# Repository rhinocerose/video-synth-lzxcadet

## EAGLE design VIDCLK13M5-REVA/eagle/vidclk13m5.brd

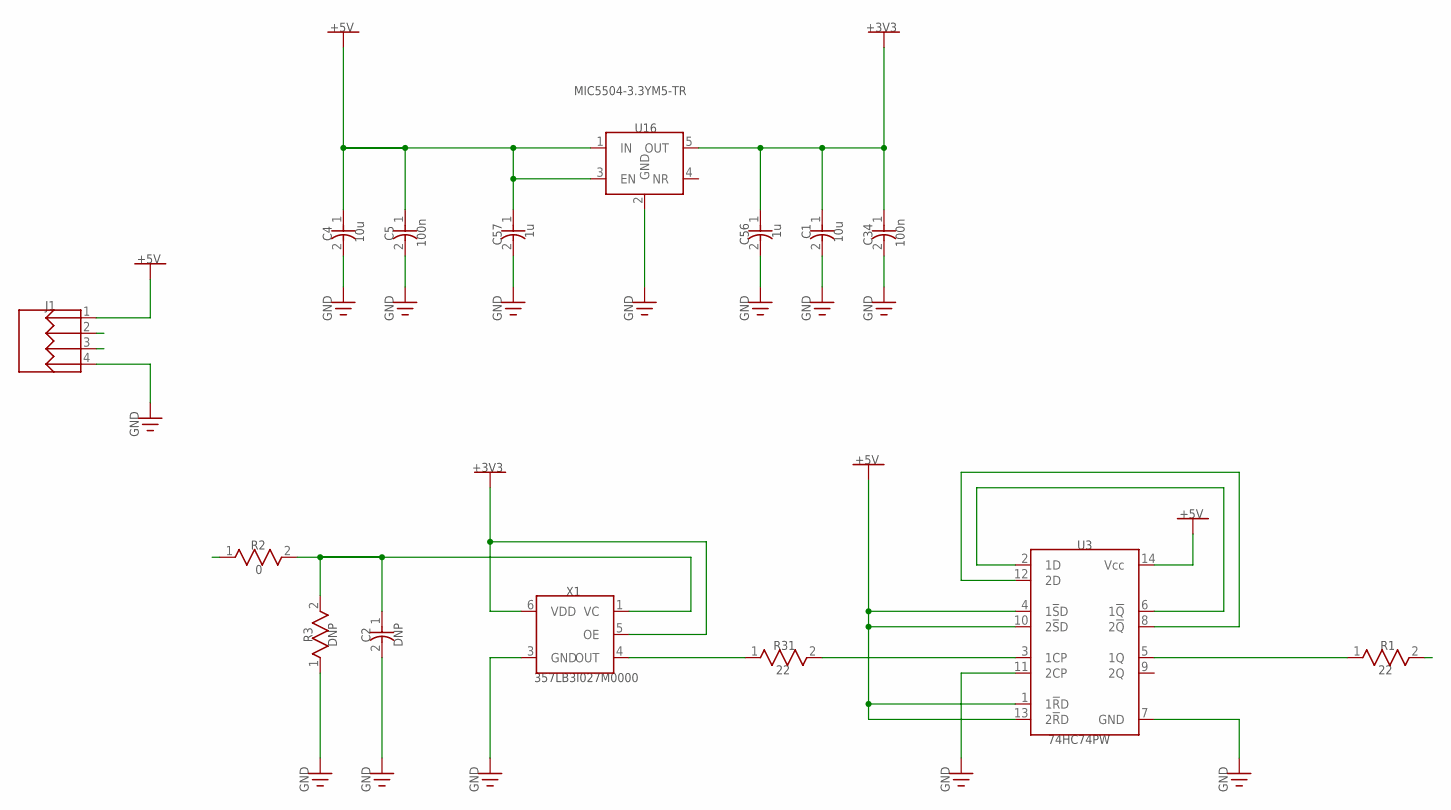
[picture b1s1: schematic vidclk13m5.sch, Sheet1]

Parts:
C1, C4: 10u; CAP_0805
C2: DNP; CAP_0603
C5, C34: 100n; CAP_0603
C56, C57: 1u; CAP_0603
J1: 644456-4; HDR-1X4T/2.54/10X2
R1, R31: 22; RES_0603_M
R2: 0; RES_0603_M
R3: DNP; RES_0603_M
U3: 74HC74PW; TSSOP-14
U16: MIC5504-3.3YM5-TR; SOT23-5
X1: 357LB3I027M0000; CSX-750V

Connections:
CLK: J1.3, R1.2
GND: C1.2, C2.2, C4.2, C5.2, C34.2, C56.2, C57.2, J1.4, R3.1, U3.7 (GND), U3.11 (2CP), U16.2 (GND), X1.3 (GND)
Net_1: U3.8 (2!Q!), U3.12 (2D)
Net_2: U3.2 (1D), U3.6 (1!Q!)
Net_3: C1.1, C34.1, C56.1, U16.5 (OUT), X1.5 (OE), X1.6 (VDD)
Net_4: R1.1, U3.5 (1Q)
Net_5: R31.1, X1.4 (OUT)
Net_6: R31.2, U3.3 (1CP)
Net_7: C2.1, R2.2, R3.2, X1.1 (VC)
Net_8: C4.1, C5.1, C57.1, J1.1, U3.1 (1!R!D), U3.4 (1!S!D), U3.10 (2!S!D), U3.13 (2!R!D), U3.14 (Vcc), U16.1 (IN), U16.3 (EN)
VC: J1.2, R2.1

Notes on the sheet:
R31
+5V
357LB3I027M0000
GND
74HC74PW
+3V3
10u
DNP
C56
C57
U16
MIC5504-3.3YM5-TR
100n
C34

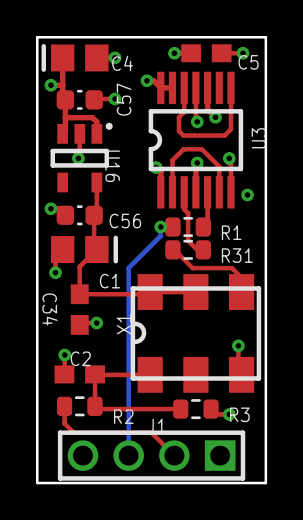
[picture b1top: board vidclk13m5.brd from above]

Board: 4 copper layers, 12.7 x 24.8 mm, 15 parts (0 on the bottom side), 11 nets.

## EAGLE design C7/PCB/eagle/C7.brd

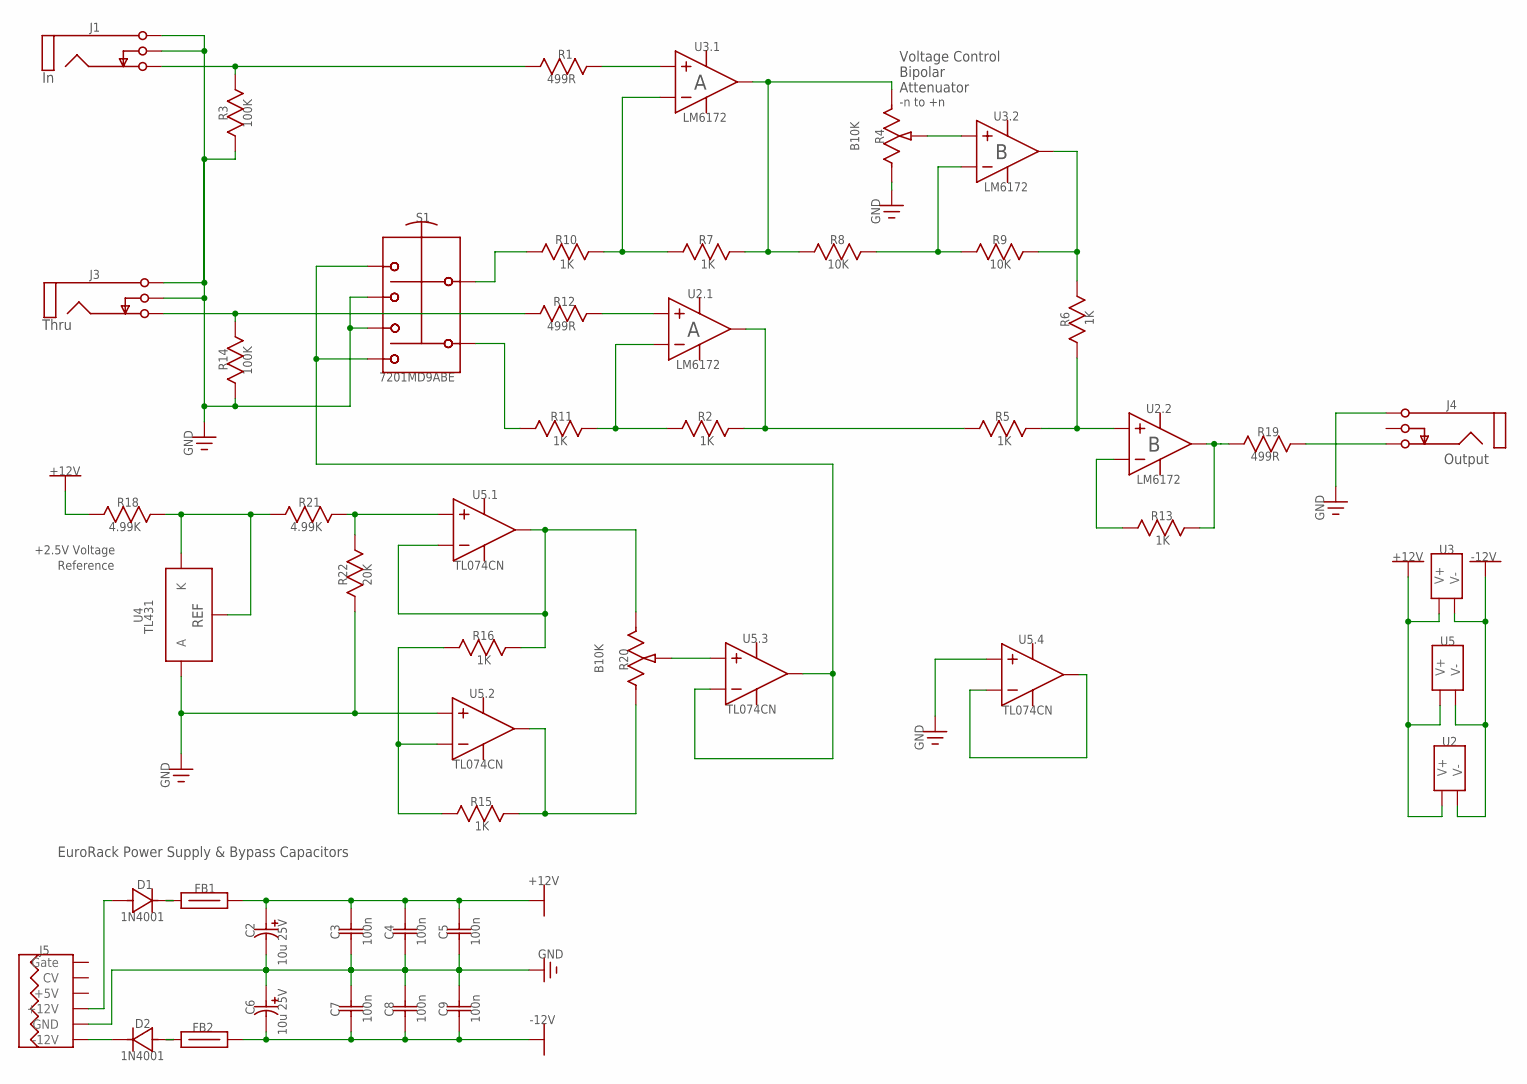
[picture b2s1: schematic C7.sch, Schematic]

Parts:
C2, C6: 10u 25V; CAPPR-2/5.08
C3, C4, C5, C7, C8, C9: 100n; CAP-2.54/6.6X3
D1, D2: 1N4001; DO-41
FB1, FB2: 68R; FB-10.16/4.45X3.5
J1, J3: PJ302M
J4: PJ302M_2; PJ302M
J5: EUROPWR16; IDC16M
R1, R12, R19: 499R; RES-7.62/5.1X2.5
R2, R5, R6, R7, R10, R11, R13, R15, R16: 1K; RES-7.62/5.1X2.5
R3, R14: 100K; RES-7.62/5.1X2.5
R4, R20: B10K; ALPHA9H
R8, R9: 10K; RES-7.62/5.1X2.5
R18, R21: 4.99K; RES-7.62/5.1X2.5
R22: 20K; RES-7.62/5.1X2.5
S1: 7201MD9ABE; 7201-A
U2, U3: LM6172; DIP-8
U4: TL431; TO-92-100R
U5: TL074CN; DIP-14

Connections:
0V: C2.2 (MINUS), C3.2, C4.2, C5.2, C6.1 (PLUS), C7.1, C8.1, C9.1, J1.1A (Sleeve), J1.1B (Sleeve), J1.2A (Switch), J1.2B (Switch), J3.1A (Sleeve), J3.1B (Sleeve), J3.2A (Switch), J3.2B (Switch), J4.1A (Sleeve), J4.1B (Sleeve), J5.3 (GND), J5.4 (GND), J5.5 (GND), J5.6, J5.7, J5.8, R3.1 (A), R4.1 (CCW), R14.1 (A), R22.2 (B), S1.3, S1.3B (3), S1.4, S1.4B (4), U4.2 (A), U5.5 (IN+), U5.12 (IN+)
+12V: C2.1 (PLUS), C3.1, C4.1, C5.1, FB1.2, R18.2 (B), U2.8 (V+), U3.8 (V+), U5.4 (V+)
-12V: C6.2 (MINUS), C7.2, C8.2, C9.2, FB2.2, U2.4 (V-), U3.4 (V-), U5.11 (V-)
BUFFERED_VC_TO_FADER: R6.2 (B), R9.2 (B), U3.7 (OUT)
Net_0: R12.2 (B), U2.3 (IN+)
Net_1: D2.2 (A), FB2.1
Net_2: D1.1 (K), FB1.1
Net_3: R2.1 (A), R11.2 (B), U2.2 (IN-)
Net_4: R16.2 (B), R20.1 (CCW), U5.1 (OUT), U5.2 (IN-)
Net_5: D2.1 (K), J5.1 (-12V), J5.2 (-12V)
Net_6: R15.2 (B), R20.3 (CW), U5.7 (OUT)
Net_7: R20.2 (W), U5.10 (IN+)
Net_8: S1.1, S1.1B (1), S1.6, S1.6B (6), U5.8 (OUT), U5.9 (IN-)
Net_9: J5.11 (+5V), J5.12 (+5V)
Net_10: R1.2 (B), U3.3 (IN+)
Net_11: J5.13 (CV), J5.14 (CV)
Net_21: R13.2 (B), R19.1 (A), U2.7 (OUT)
Net_23: R4.2 (W), U3.5 (IN+)
Net_24: R2.2 (B), R5.1 (A), U2.1 (OUT)
Net_25: R13.1 (A), U2.6 (IN-)
Net_26: R5.2 (B), R6.1 (A), U2.5 (IN+)
Net_27: R15.1 (A), R16.1 (A), U5.6 (IN-)
Net_28: R10.1 (A), S1.2 (COMM), S1.2B (COMM)
Net_29: U5.13 (IN-), U5.14 (OUT)
Net_30: R21.1 (A), R22.1 (A), U5.3 (IN+)
Net_31: R11.1 (A), S1.5 (COMM), S1.5B (COMM)
Net_32: J4.2A (Switch), J4.2B (Switch)
Net_33: D1.2 (A), J5.9 (+12V), J5.10 (+12V)
Net_34: J4.3A (Tip), J4.3B (Tip), R19.2 (B)
Net_35: J5.15 (Gate), J5.16 (Gate)
Net_50: R18.1 (A), R21.2 (B), U4.1 (K), U4.3 (REF)
Net_52: R7.1 (A), R10.2 (B), U3.2 (IN-)
Net_53: R4.3 (CW), R7.2 (B), R8.1 (A), U3.1 (OUT)
Net_54: R8.2 (B), R9.1 (A), U3.6 (IN-)
Net_58: J1.3A (Tip), J1.3B (Tip), R1.1 (A), R3.2 (B)
Net_64: J3.3A (Tip), J3.3B (Tip), R12.1 (A), R14.2 (B)

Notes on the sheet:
EuroRack Power Supply & Bypass Capacitors
Output
+2.5V Voltage
Attenuator
Bipolar
-n to +n
Reference
Thru
Voltage Control
10u 25V
100n
1N4001
FB1
FB2
GND
+12V
-12V
499R
100K
B10K
10K
R10
R11
R12
R13
R14
R15
R16
7201MD9ABE
R18
4.99K
R19
R20
R21
R22
20K
U2.1
LM6172
U2.2
U3.1

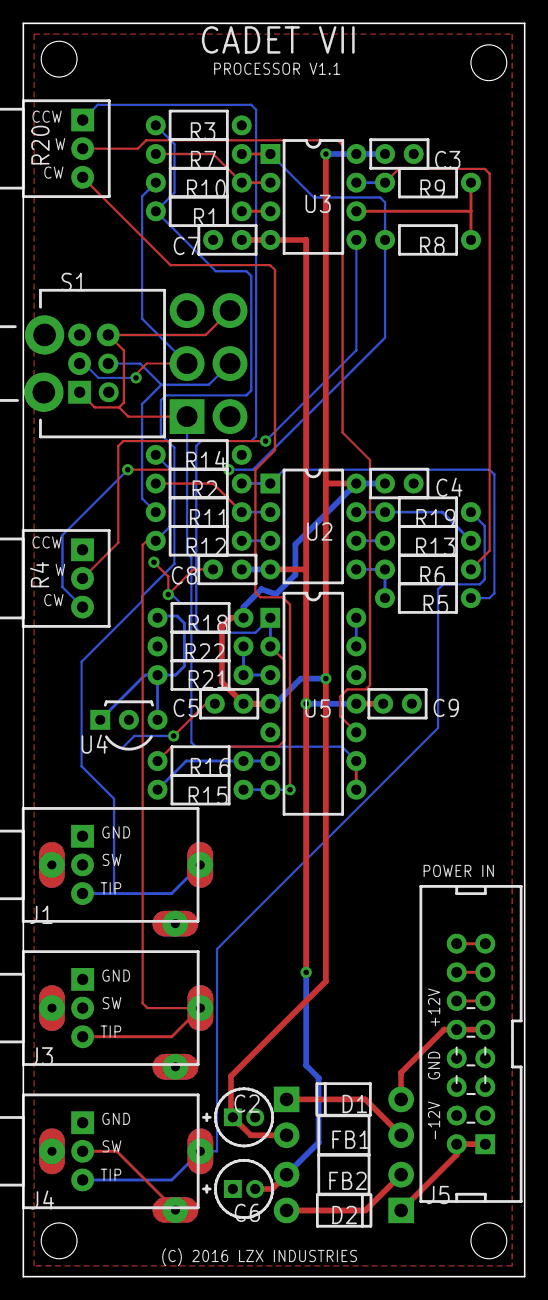
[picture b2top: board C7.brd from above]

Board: 2 copper layers, 44.5 x 111.1 mm, 42 parts (0 on the bottom side), 36 nets.

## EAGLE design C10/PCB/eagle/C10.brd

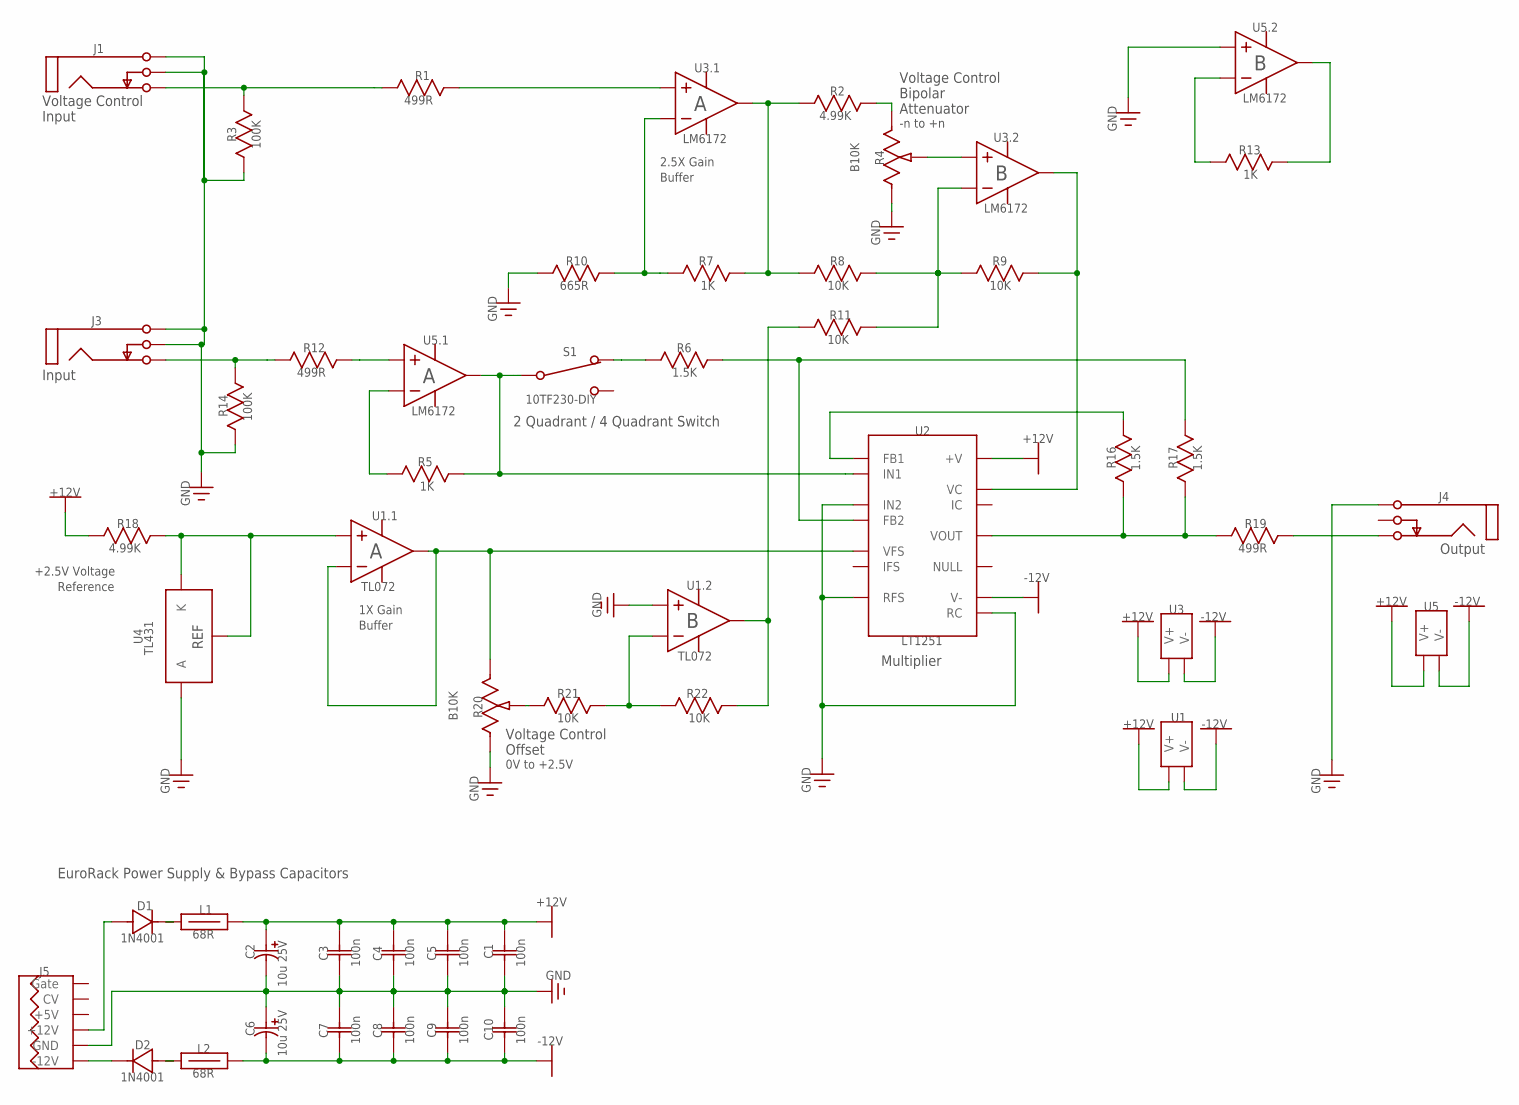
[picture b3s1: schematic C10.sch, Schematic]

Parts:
C1, C3, C4, C5, C7, C8, C9, C10: 100n; CAP-2.54/6.6X3
C2, C6: 10u 25V; CAPPR-2/5.08
D1, D2: 1N4001; DO-41
J1, J3: PJ302M
J4: PJ302M_1; PJ302M
J5: EUROPWR16; IDC16M
L1, L2: 68R; FB-10.16/4.45X3.5
R1, R12, R19: 499R; RES-7.62/5.1X2.5
R2, R18: 4.99K; RES-7.62/5.1X2.5
R3, R14: 100K; RES-7.62/5.1X2.5
R4, R20: B10K; ALPHA9H
R5, R7, R13: 1K; RES-7.62/5.1X2.5
R6, R16, R17: 1.5K; RES-7.62/5.1X2.5
R8, R9, R11, R21, R22: 10K; RES-7.62/5.1X2.5
R10: 665R; RES-7.62/5.1X2.5
S1: 10TF230-DIY
U1: TL072; DIP-8
U2: LT1251; DIP-14
U3, U5: LM6172; DIP-8
U4: TL431; TO-92-100R

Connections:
0V: C1.2, C2.2 (MINUS), C3.2, C4.2, C5.2, C6.1 (PLUS), C7.1, C8.1, C9.1, C10.1, J1.1A (Sleeve), J1.1B (Sleeve), J1.2A (Switch), J1.2B (Switch), J3.1A (Sleeve), J3.1B (Sleeve), J3.2A (Switch), J3.2B (Switch), J4.1A (Sleeve), J4.1B (Sleeve), J5.3 (GND), J5.4 (GND), J5.5 (GND), J5.6, J5.7, J5.8, R3.1 (A), R4.1 (CCW), R10.1 (A), R14.1 (A), R20.1 (CCW), U1.5 (IN+), U2.5 (RC), U2.10 (RFS), U2.14 (IN2), U4.2 (A), U5.5 (IN+)
+2.5V_Reference: R20.3 (CW), U1.1 (OUT), U1.2 (IN-), U2.12 (VFS)
+12V: C1.1, C2.1 (PLUS), C3.1, C4.1, C5.1, L1.2, R18.2 (B), U1.8 (V+), U2.9 (+V), U3.8 (V+), U5.8 (V+)
-12V: C6.2 (MINUS), C7.2, C8.2, C9.2, C10.2, L2.2, U1.4 (V-), U2.7 (V-), U3.4 (V-), U5.4 (V-)
BIAS_CTRL_BUFFERED: R11.1 (A), R22.2 (B), U1.7 (OUT)
BUFFERED_VC_TO_FADER: R9.2 (B), U2.3 (VC), U3.7 (OUT)
Net_0: R6.1 (A), S1.1 (C3), S1.1B (C3)
Net_1: D2.2 (A), L2.1
Net_2: D1.1 (K), L1.1
Net_3: J5.13 (CV), J5.14 (CV)
Net_4: J5.15 (Gate), J5.16 (Gate)
Net_5: D2.1 (K), J5.1 (-12V), J5.2 (-12V)
Net_10: R1.2 (B), U3.3 (IN+)
Net_13: R12.2 (B), U5.3 (IN+)
Net_17: R2.2 (B), R4.3 (CW)
Net_23: R4.2 (W), U3.5 (IN+)
Net_26: R5.1 (A), U5.2 (IN-)
Net_27: R5.2 (B), S1.2 (C1), S1.2B (C1), U2.1 (IN1), U5.1 (OUT)
Net_28: R20.2 (W), R21.1 (A)
Net_29: R13.1 (A), U5.6 (IN-)
Net_30: R13.2 (B), U5.7 (OUT)
Net_31: J4.2A (Switch), J4.2B (Switch)
Net_32: J5.11 (+5V), J5.12 (+5V)
Net_33: D1.2 (A), J5.9 (+12V), J5.10 (+12V)
Net_34: J4.3A (Tip), J4.3B (Tip), R19.2 (B)
Net_35: S1.3 (C2), S1.3B (C2)
Net_45: R16.1 (A), R17.2 (B), R19.1 (A), U2.8 (VOUT)
Net_46: R6.2 (B), R17.1 (A), U2.13 (FB2)
Net_49: R16.2 (B), U2.2 (FB1)
Net_50: R18.1 (A), U1.3 (IN+), U4.1 (K), U4.3 (REF)
Net_52: R7.1 (A), R10.2 (B), U3.2 (IN-)
Net_53: R2.1 (A), R7.2 (B), R8.1 (A), U3.1 (OUT)
Net_54: R8.2 (B), R9.1 (A), R11.2 (B), U3.6 (IN-)
Net_58: J1.3A (Tip), J1.3B (Tip), R1.1 (A), R3.2 (B)
Net_60: R21.2 (B), R22.1 (A), U1.6 (IN-)
Net_64: J3.3A (Tip), J3.3B (Tip), R12.1 (A), R14.2 (B)

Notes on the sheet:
EuroRack Power Supply & Bypass Capacitors
Voltage Control
2 Quadrant / 4 Quadrant Switch
Output
+2.5V Voltage
Attenuator
Offset
Bipolar
0V to +2.5V
2.5X Gain
Buffer
-n to +n
Multiplier
Reference
1X Gain
Input
10u 25V
100n
1N4001
U5.1
LM6172
68R
GND
+12V
-12V
499R
4.99K
100K
B10K
U5.2
10K
R10
665R
R11
R12
R13
R14
R16
1.5K
R17

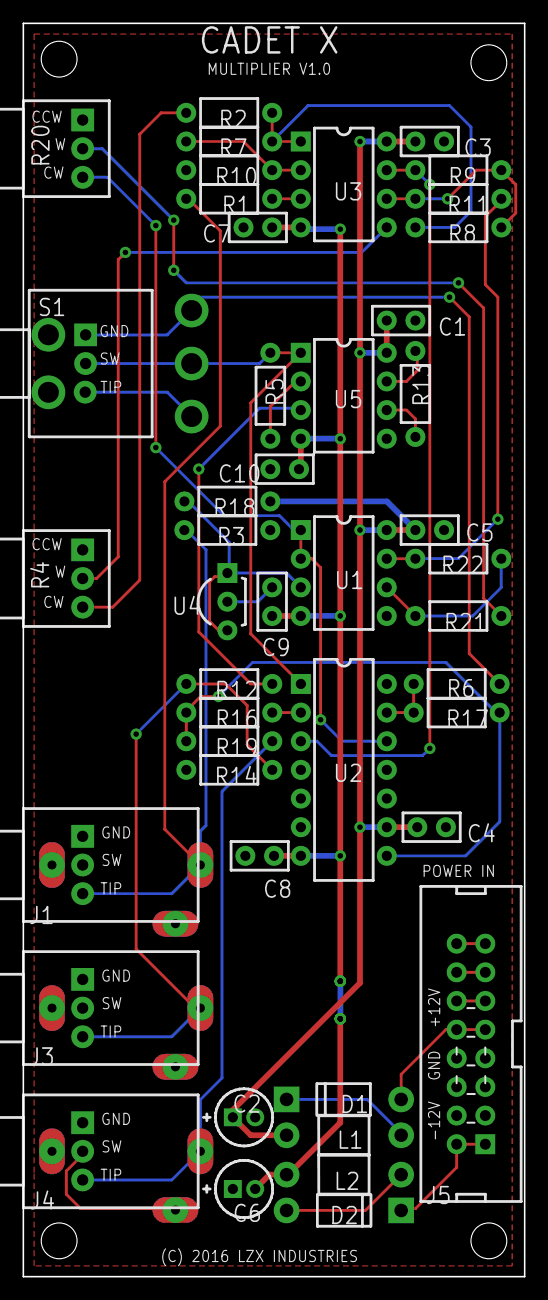
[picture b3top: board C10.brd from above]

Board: 2 copper layers, 44.5 x 111.1 mm, 45 parts (0 on the bottom side), 36 nets.

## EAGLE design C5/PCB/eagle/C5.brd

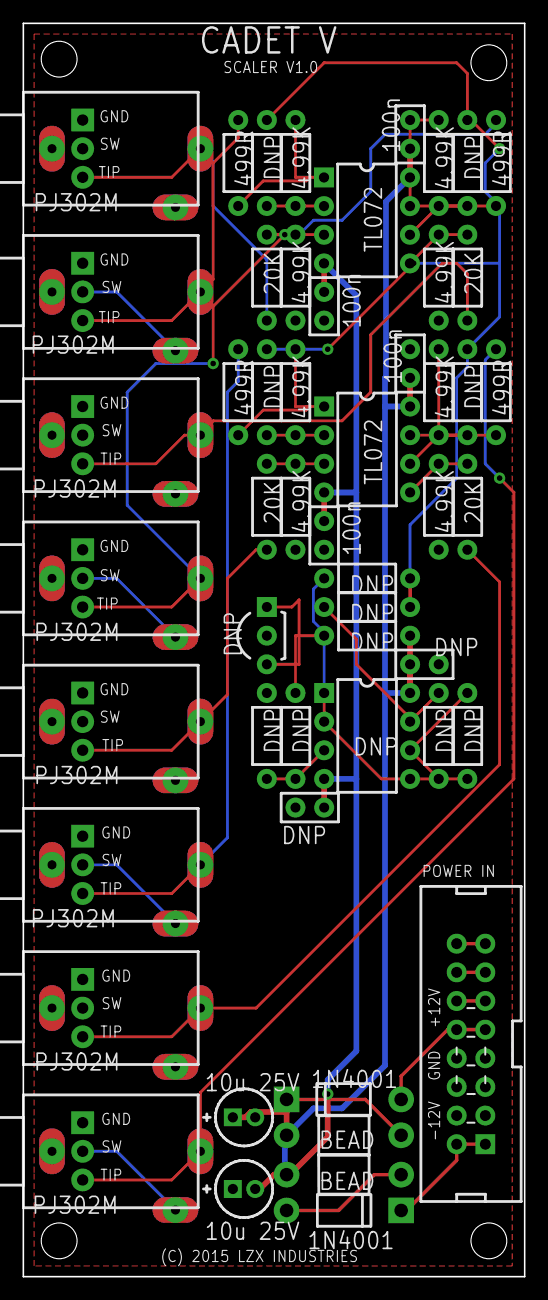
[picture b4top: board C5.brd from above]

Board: 2 copper layers, 44.5 x 111.1 mm, 52 parts (0 on the bottom side), 40 nets.

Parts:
C2: 10u 25V; CAPPR-2/5.08
C3, C4: 100n; CAP-2.54/6.6x3
C5: DNP; CAP-2.54/6.6x3_C5
C6: 10u 25V; CAPPR-2/5.08_C6
C7, C8: 100n; CAP-2.54/6.6x3_C7
C9: DNP; CAP-2.54/6.6x3_C9
D1: 1N4001; DO-41
D2: 1N4001; DO-41_D2
J1, J2, J3, J4, J5, J6, J7, J8: PJ302M
J9: EUROPWR16; IDC16M
L1, L2: BEAD; FB-10.16/4.45x3.5
R1, R3, R15, R17: 20K; RES-7.62/5.1x2.5
R2, R5, R16, R19: 499R; RES-7.62/5.1x2.5
R4, R6, R12, R14, R18, R20, R26, R28: 4.99K; RES-7.62/5.1x2.5
R7, R8, R9, R10, R11, R13, R25, R27: DNP; RES-7.62/5.1x2.5_R11
R29, R30, R31: DNP; RES-7.62/5.1x2.5
U1, U2: TL072; DIP-8_U1
U3: DNP; TO-92-100R
U4: DNP; DIP-8

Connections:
0V: C2.2, C3.2, C4.2, C5.2, C6.1, C7.1, C8.1, C9.1, J1.1A, J1.1B, J1.2A, J1.2B, J2.1A, J2.1B, J3.1A, J3.1B, J3.2A, J3.2B, J4.1A, J4.1B, J5.1A, J5.1B, J5.2A, J5.2B, J6.1A, J6.1B, J7.1A, J7.1B, J7.2A, J7.2B, J8.1A, J8.1B, J9.3, J9.4, J9.5, J9.6, J9.7, J9.8, R4.1, R6.1, R18.1, R20.1, R31.2, U3.2, U4.5
+12V: C2.1, C3.1, C4.1, C5.1, L1.2, R29.2, U1.8, U2.8, U4.8
-12V: C6.2, C7.2, C8.2, C9.2, L2.2, U1.4, U2.4, U4.4
Net_0: R30.1, R31.1, U4.3
Net_1: D2.2, L2.1
Net_2: D1.1, L1.1
Net_3: J3.3A, J3.3B, R3.1
Net_4: R7.2, R8.1, U4.6
Net_5: D2.1, J9.1, J9.2
Net_6: R3.2, R6.2, U1.5
Net_7: J4.3A, J4.3B, R5.2
Net_8: J1.3A, J1.3B, R1.1
Net_9: R1.2, R4.2, U1.3
Net_10: R13.2, R14.1, U1.6
Net_11: J2.3A, J2.3B, R2.2
Net_12: R5.1, R14.2, U1.7
Net_13: J2.2A, J2.2B
Net_18: J5.3A, J5.3B, R15.1
Net_19: R15.2, R18.2, U2.3
Net_20: J6.3A, J6.3B, R16.2
Net_21: R25.2, R26.1, U2.2
Net_22: R16.1, R26.2, U2.1
Net_23: J7.3A, J7.3B, R17.1
Net_24: R17.2, R20.2, U2.5
Net_25: J8.3A, J8.3B, R19.2
Net_26: R27.2, R28.1, U2.6
Net_27: R19.1, R28.2, U2.7
Net_31: R8.2, R10.2, U4.1, U4.2
Net_32: R7.1, R9.2, U4.7
Net_33: D1.2, J9.9, J9.10
Net_34: J9.11, J9.12
Net_35: J9.13, J9.14
Net_36: J9.15, J9.16
Net_37: J4.2A, J4.2B
Net_38: J6.2A, J6.2B
Net_39: J8.2A, J8.2B
Net_50: R29.1, R30.2, U3.1, U3.3
Net_52: R11.2, R12.1, U1.2
Net_53: R2.1, R12.2, U1.1
VREF: R9.1, R10.1, R11.1, R13.1, R25.1, R27.1

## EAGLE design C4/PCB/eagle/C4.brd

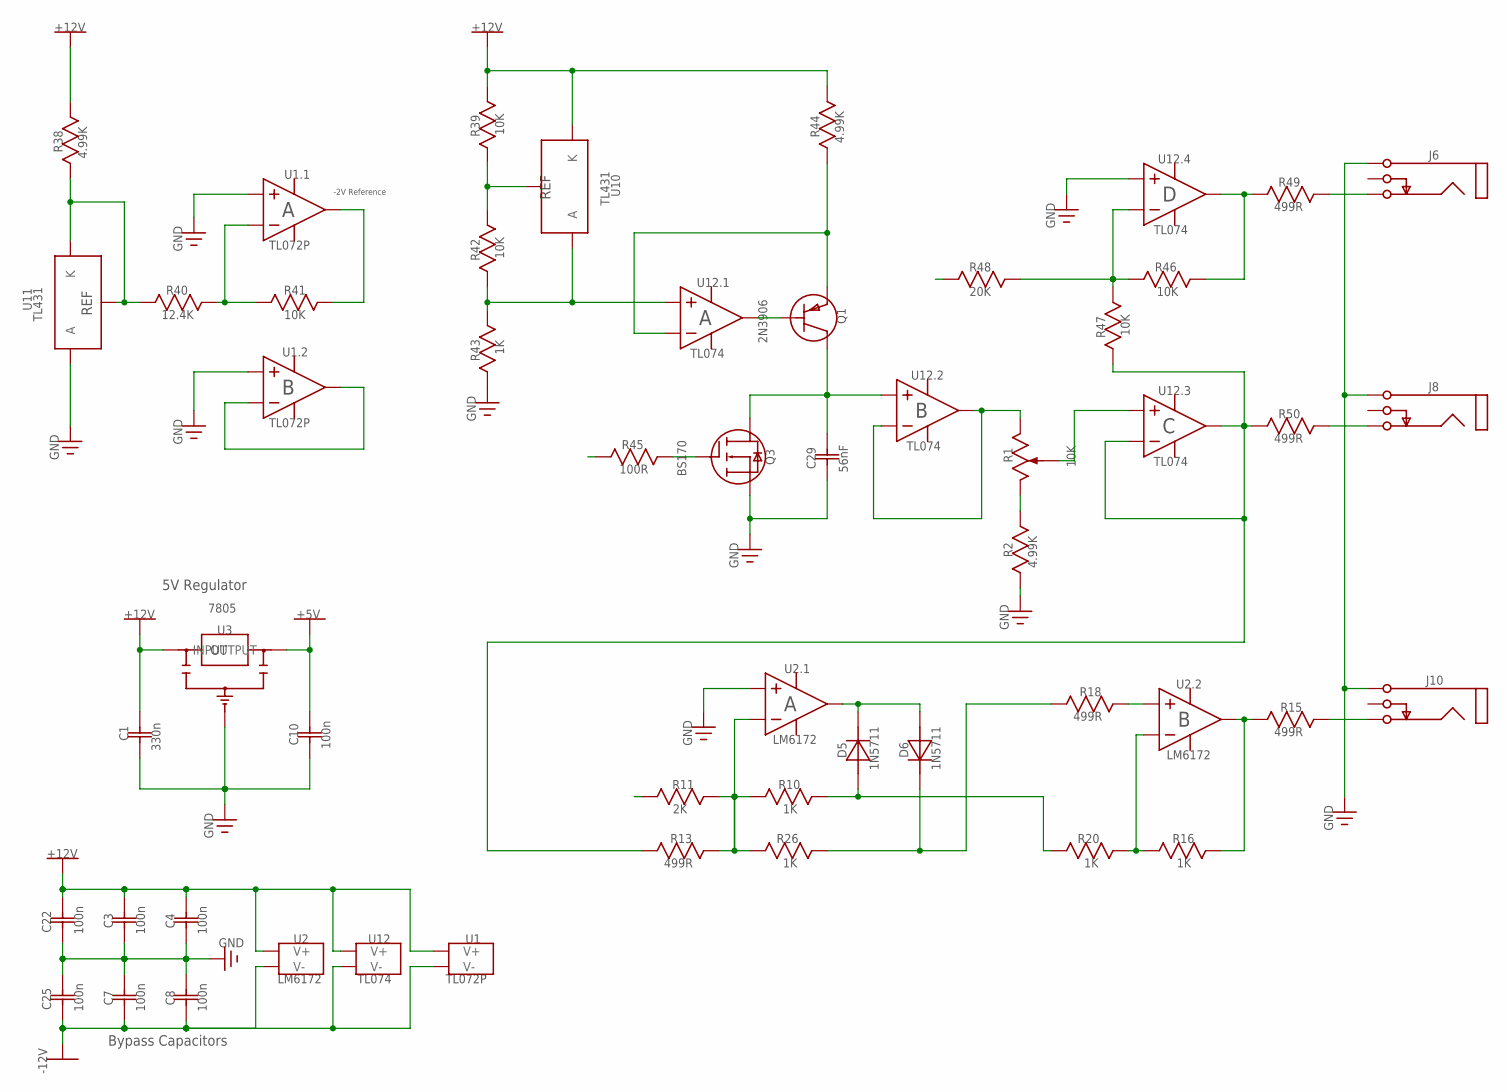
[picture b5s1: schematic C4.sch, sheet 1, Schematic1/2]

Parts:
C1: 330n; CAP-2.54/6.6X3
C3, C4, C7, C8, C10, C22, C25: 100n; CAP-2.54/6.6X3
C29: 56nF; CAP-2.54/6.6X3
D5, D6: 1N5711; DO-35
J6, J8, J10: 3.5MM_JACK; PJ302M
Q1: 2N3906; TO-92
Q3: BS170; TO-92
R1: 10K; 3362P
R2, R38, R44: 4.99K; RES-7.62/5.1X2.5
R10, R16, R20, R26, R43: 1K; RES-7.62/5.1X2.5
R11: 2K; RES-7.62/5.1X2.5
R13, R15, R18, R49, R50: 499R; RES-7.62/5.1X2.5
R39, R41, R42, R46, R47: 10K; RES-7.62/5.1X2.5
R40: 12.4K; RES-7.62/5.1X2.5
R45: 100R; RES-7.62/5.1X2.5
R48: 20K; RES-7.62/5.1X2.5
U1: TL072P; DIP-8
U2: LM6172; DIP-8
U3: 7805; TO-220H
U10: TL431; TO-92-100R
U11: TL431_16; TO-92-100R
U12: TL074; DIP-14

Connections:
0V: C1.2, C3.2, C4.2, C7.1, C8.1, C10.2, C22.2, C25.1, C29.2, J6.1A (Sleeve), J6.1B (Sleeve), J8.1A (Sleeve), J8.1B (Sleeve), J10.1A (Sleeve), J10.1B (Sleeve), Q3.3 (S), R2.2 (B), R43.1 (A), U1.3 (IN+), U1.5 (IN+), U2.3 (IN+), U3.2 (GND), U11.2 (A), U12.12 (IN+); also elsewhere on the board
+5V: C10.1, U3.3 (OUTPUT); also elsewhere on the board
+12V: C1.1, C3.1, C4.1, C22.1, R38.2 (B), R39.2 (B), R44.2 (B), U1.8 (V+), U2.8 (V+), U3.1 (INPUT), U10.1 (K), U12.4 (V+); also elsewhere on the board
-2V_Reference: R11.1 (A), R41.2 (B), R48.1 (A), U1.1 (OUT); also elsewhere on the board
-12V: C7.2, C8.2, C25.2, U1.4 (V-), U2.4 (V-), U12.11 (V-); also elsewhere on the board
Net_3: U1.6 (IN-), U1.7 (OUT)
Net_7: J6.2A (Switch), J6.2B (Switch)
Net_8: R39.1 (A), R42.2 (B), U10.3 (REF)
Net_9: J8.2A (Switch), J8.2B (Switch)
Net_16: R18.2 (B), U2.5 (IN+)
Net_17: R15.2 (B), R16.2 (B), U2.7 (OUT)
Net_21: R10.1 (A), R11.2 (B), R13.2 (B), R26.1 (A), U2.2 (IN-)
Net_22: D5.1 (K), D6.2 (A), U2.1 (OUT)
Net_40: R46.1 (A), R49.2 (B), U12.14 (OUT)
Net_45: D5.2 (A), R10.2 (B), R20.1 (A)
Net_46: D6.1 (K), R18.1 (A), R26.2 (B)
Net_51: Q3.2 (G), R45.1 (A)
Net_57: J6.3A (Tip), J6.3B (Tip), R49.1 (A)
Net_58: J8.3A (Tip), J8.3B (Tip), R50.1 (A)
Net_59: J10.3A (Tip), J10.3B (Tip), R15.1 (A)
Net_60: R1.2 (W), U12.10 (IN+)
Net_61: R1.1 (CCW), R2.1 (A)
Net_67: R38.1 (A), R40.1 (A), U11.1 (K), U11.3 (REF)
Net_68: R40.2 (B), R41.1 (A), U1.2 (IN-)
Net_72: J10.2A (Switch), J10.2B (Switch)
Net_73: R42.1 (A), R43.2 (B), U10.2 (A), U12.3 (IN+)
Net_74: Q1.1 (E), R44.1 (A), U12.2 (IN-)
Net_75: Q1.2 (B), U12.1 (OUT)
Net_76: C29.1, Q1.3 (C), Q3.1 (D), U12.5 (IN+)
Net_78: R1.3 (CW), U12.6 (IN-), U12.7 (OUT)
Net_80: R13.1 (A), R47.2 (B), R50.2 (B), U12.8 (OUT), U12.9 (IN-)
Net_81: R46.2 (B), R47.1 (A), R48.2 (B), U12.13 (IN-)
Net_83: R16.1 (A), R20.2 (B), U2.6 (IN-)
_HSYNC: R45.2 (B); also elsewhere on the board

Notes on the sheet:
5V Regulator
Bypass Capacitors
-2V Reference
330n
100n
C10
C22
C25
C29
56nF
1N5711
J10
+12V
GND
+5V
-12V
2N3906
BS170
10K
4.99K
R10
R11
R13
499R
R15
R16
R18
R20
R26
R38
R39
R40
12.4K
R41
R42
R43
R44
R45
100R
R46

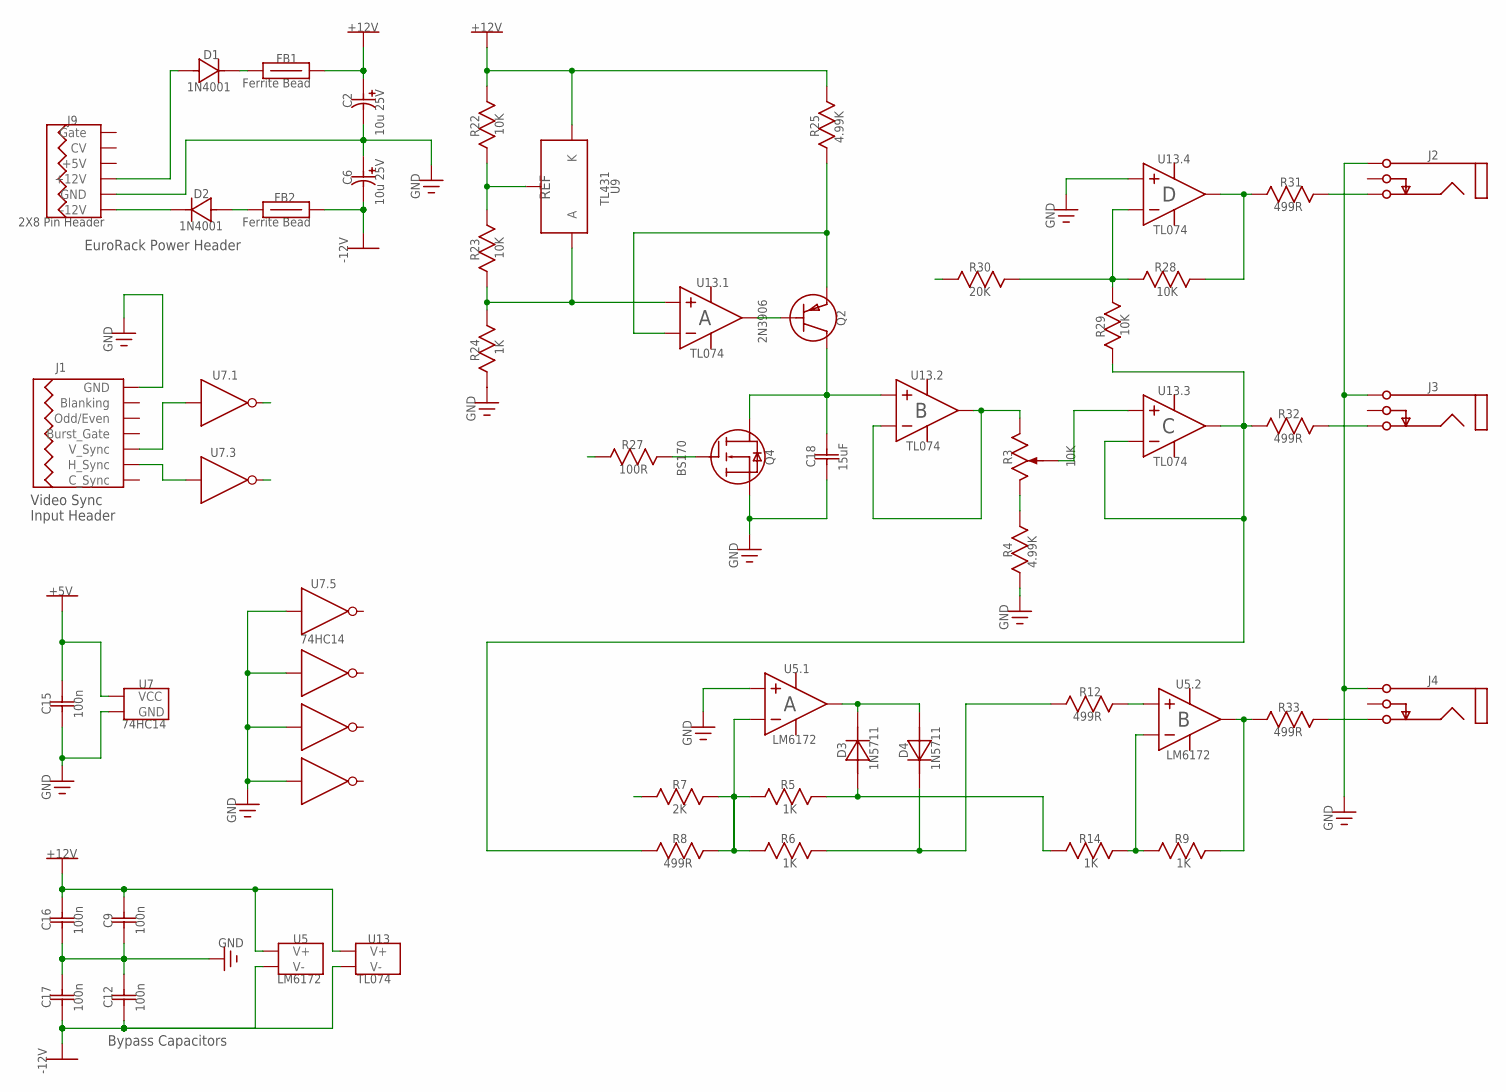
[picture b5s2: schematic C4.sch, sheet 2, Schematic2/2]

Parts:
C2, C6: 10u 25V; CAPPR-2/5.08
C9, C12, C15, C16, C17: 100n; CAP-2.54/6.6X3
C18: 15uF; CAP-2.54/6.6X3
D1, D2: 1N4001; DO-41
D3, D4: 1N5711; DO-35
FB1, FB2: 68R; FB-10.16/4.45X3.5
J1: LZXSYNC14; IDC14M
J2, J3, J4: 3.5MM_JACK; PJ302M
J9: 2X8_PIN_HEADER; IDC16M
Q2: 2N3906; TO-92
Q4: BS170; TO-92
R3: 10K; 3362P
R4, R25: 4.99K; RES-7.62/5.1X2.5
R5, R6, R9, R14, R24: 1K; RES-7.62/5.1X2.5
R7: 2K; RES-7.62/5.1X2.5
R8, R12, R31, R32, R33: 499R; RES-7.62/5.1X2.5
R22, R23, R28, R29: 10K; RES-7.62/5.1X2.5
R27: 100R; RES-7.62/5.1X2.5
R30: 20K; RES-7.62/5.1X2.5
U5: LM6172; DIP-8
U7: 74HC14; DIP-14
U9: TL431; TO-92-100R
U13: TL074; DIP-14

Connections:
0V: C2.2 (MINUS), C6.1 (PLUS), C9.2, C12.1, C15.2, C16.2, C17.1, C18.2, J1.1 (GND), J1.2 (GND), J2.1A (Sleeve), J2.1B (Sleeve), J3.1A (Sleeve), J3.1B (Sleeve), J4.1A (Sleeve), J4.1B (Sleeve), J9.3 (GND), J9.4 (GND), J9.5 (GND), J9.6, J9.7, J9.8, Q4.3 (S), R4.2 (B), R24.1 (A), U5.3 (IN+), U7.3 (A), U7.7 (GND), U7.9 (A), U7.11 (A), U7.13 (A), U13.12 (IN+); also elsewhere on the board
+5V: C15.1, U7.14 (VCC); also elsewhere on the board
+12V: C2.1 (PLUS), C9.1, C16.1, FB1.2, R22.2 (B), R25.2 (B), U5.8 (V+), U9.1 (K), U13.4 (V+); also elsewhere on the board
-2V_Reference: R7.1 (A), R30.1 (A); also elsewhere on the board
-12V: C6.2 (MINUS), C12.2, C17.2, FB2.2, U5.4 (V-), U13.11 (V-); also elsewhere on the board
Net_0: J1.7 (Burst_Gate), J1.8 (Burst_Gate)
Net_1: D2.2 (A), FB2.1
Net_2: D1.1 (K), FB1.1
Net_4: J1.11 (H_Sync), J1.12 (H_Sync), U7.5 (A)
Net_5: D2.1 (K), J9.1 (-12V), J9.2 (-12V)
Net_6: J1.13 (C_Sync), J1.14 (C_Sync)
Net_10: R22.1 (A), R23.2 (B), U9.3 (REF)
Net_11: R12.2 (B), U5.5 (IN+)
Net_12: R9.2 (B), R33.2 (B), U5.7 (OUT)
Net_13: R5.1 (A), R6.1 (A), R7.2 (B), R8.2 (B), U5.2 (IN-)
Net_14: D3.1 (K), D4.2 (A), U5.1 (OUT)
Net_15: R28.1 (A), R31.2 (B), U13.14 (OUT)
Net_18: D3.2 (A), R5.2 (B), R14.1 (A)
Net_19: D4.1 (K), R6.2 (B), R12.1 (A)
Net_25: R23.1 (A), R24.2 (B), U9.2 (A), U13.3 (IN+)
Net_26: Q2.1 (E), R25.1 (A), U13.2 (IN-)
Net_27: Q2.2 (B), U13.1 (OUT)
Net_28: C18.1, Q2.3 (C), Q4.1 (D), U13.5 (IN+)
Net_29: Q4.2 (G), R27.1 (A)
Net_30: R3.3 (CW), U13.6 (IN-), U13.7 (OUT)
Net_31: R8.1 (A), R29.2 (B), R32.2 (B), U13.8 (OUT), U13.9 (IN-)
Net_32: R28.2 (B), R29.1 (A), R30.2 (B), U13.13 (IN-)
Net_33: D1.2 (A), J9.9 (+12V), J9.10 (+12V)
Net_34: R9.1 (A), R14.2 (B), U5.6 (IN-)
Net_35: J2.3A (Tip), J2.3B (Tip), R31.1 (A)
Net_36: J3.3A (Tip), J3.3B (Tip), R32.1 (A)
Net_37: J4.3A (Tip), J4.3B (Tip), R33.1 (A)
Net_38: R3.2 (W), U13.10 (IN+)
Net_39: R3.1 (CCW), R4.1 (A)
Net_56: J1.9 (V_Sync), J1.10 (V_Sync), U7.1 (A)
Net_62: J1.5 (Odd/Even), J1.6 (Odd/Even)
Net_63: J1.3 (Blanking), J1.4 (Blanking)
Net_64: J2.2A (Switch), J2.2B (Switch)
Net_65: J3.2A (Switch), J3.2B (Switch)
Net_66: J4.2A (Switch), J4.2B (Switch)
Net_69: J9.11 (+5V), J9.12 (+5V)
Net_70: J9.13 (CV), J9.14 (CV)
Net_71: J9.15 (Gate), J9.16 (Gate)
_HSYNC: U7.6 (Y); also elsewhere on the board
_VSYNC: R27.2 (B), U7.2 (Y)

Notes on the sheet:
EuroRack Power Header
Video Sync
Input Header
Bypass Capacitors
10u 25V
100n
C12
C15
C16
C17
C18
15uF
1N4001
1N5711
FB1
Ferrite Bead
FB2
2X8 Pin Header
GND
+12V
-12V
+5V
2N3906
BS170
10K
4.99K
499R
R12
R14
R22
R23
R24
R25
R27
100R
R28
R29
R30
20K
R31

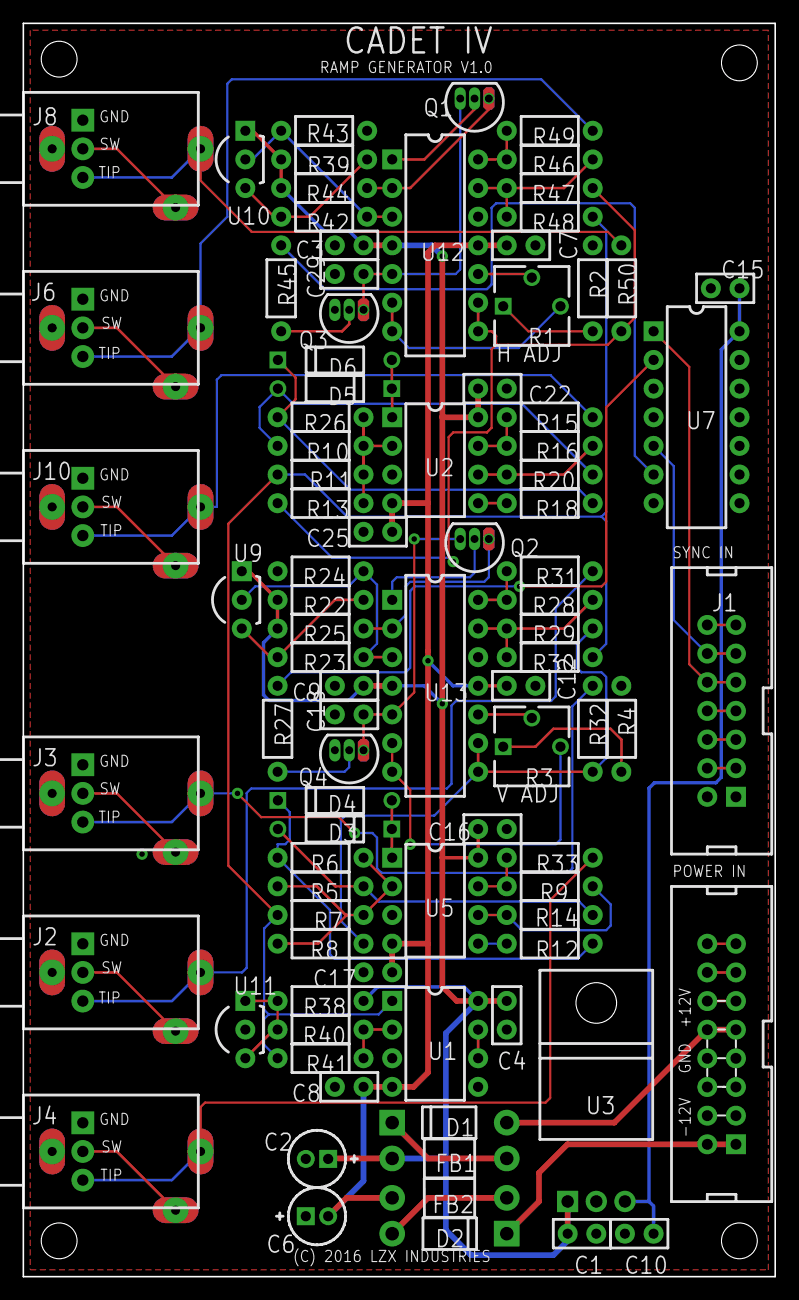
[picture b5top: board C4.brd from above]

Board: 2 copper layers, 66.7 x 111.1 mm, 90 parts (0 on the bottom side), 73 nets.

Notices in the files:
C1/PCB/eagle/C1.brd:
(C) 2016 LZX INDUSTRIES
C5/PCB/eagle/C5.brd:
(C) 2015 LZX INDUSTRIES
